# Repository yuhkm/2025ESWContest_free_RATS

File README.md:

# 2025ESWContest_free_RATS
<br/>

## Driving Assistance Device for Beginner Drivers

<br/>

## System Overview

<br/>

## Team Members
<div align="center">

| **안재원 (팀장)** | **김유환** | **박요한** | **박수현** | **정연홍** |
|:---:|:---:|:---:|:---:|:---:|
|  |  |  |  |  |
| [@JwAhn0830](https://github.com/JwAhn0830) | [@yuhkm](https://github.com/yuhkm) | [@doct-vg](https://github.com/doct-vg) | [@jstrfunctionk](https://github.com/strfunctionk) | [@zyh3569](https://github.com/zyh3569) |
| [Main Device (Gaze),](https://github.com/yuhkm/2025ESWContest_free_RATS/tree/main/Main_Device/gaze)<br/>[Server Communication](https://github.com/yuhkm/2025ESWContest_free_RATS/tree/main/Main_Device) | [Main Device (Lane),](https://github.com/yuhkm/2025ESWContest_free_RATS/tree/main/Main_Device/LDS)<br/>[HUD](https://github.com/yuhkm/2025ESWContest_free_RATS/tree/main/HUD) | [Vehicle Sensors,](https://github.com/yuhkm/2025ESWContest_free_RATS/tree/main/Main_Device/VDP)<br/>[CAD](https://github.com/yuhkm/2025ESWContest_free_RATS/tree/main/HW) | [Backend](https://github.com/yuhkm/2025ESWContest_free_RATS/tree/main/Backend) | [Frontend](https://github.com/yuhkm/2025ESWContest_free_RATS/tree/main/Frontend) |

</div>
<br/>

## Demo
- [YouTube](https://www.youtube.com/watch?v=WTc7l_RPrZw)  
<br/>

## Repo
- [Main Device](https://github.com/yuhkm/2025ESWContest_free_RATS/tree/main/Main_Device)  
- [HUD](https://github.com/yuhkm/2025ESWContest_free_RATS/tree/main/HUD)
- [Backend](https://github.com/yuhkm/2025ESWContest_free_RATS/tree/main/Backend)  
- [Frontend](https://github.com/yuhkm/2025ESWContest_free_RATS/tree/main/Frontend)  
- [HW](https://github.com/yuhkm/2025ESWContest_free_RATS/tree/main/HW)
<br/>

<br/>

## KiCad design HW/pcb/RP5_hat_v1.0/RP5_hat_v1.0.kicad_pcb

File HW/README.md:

# HW
- CAD
  - SolidWorks
- PCB
  - KiCAD  

<br>

## CAD

### Raspberry Pi 5 case  

### HUD case  

### Camera case  

### IMU case  

<br>
<br>

## PCB

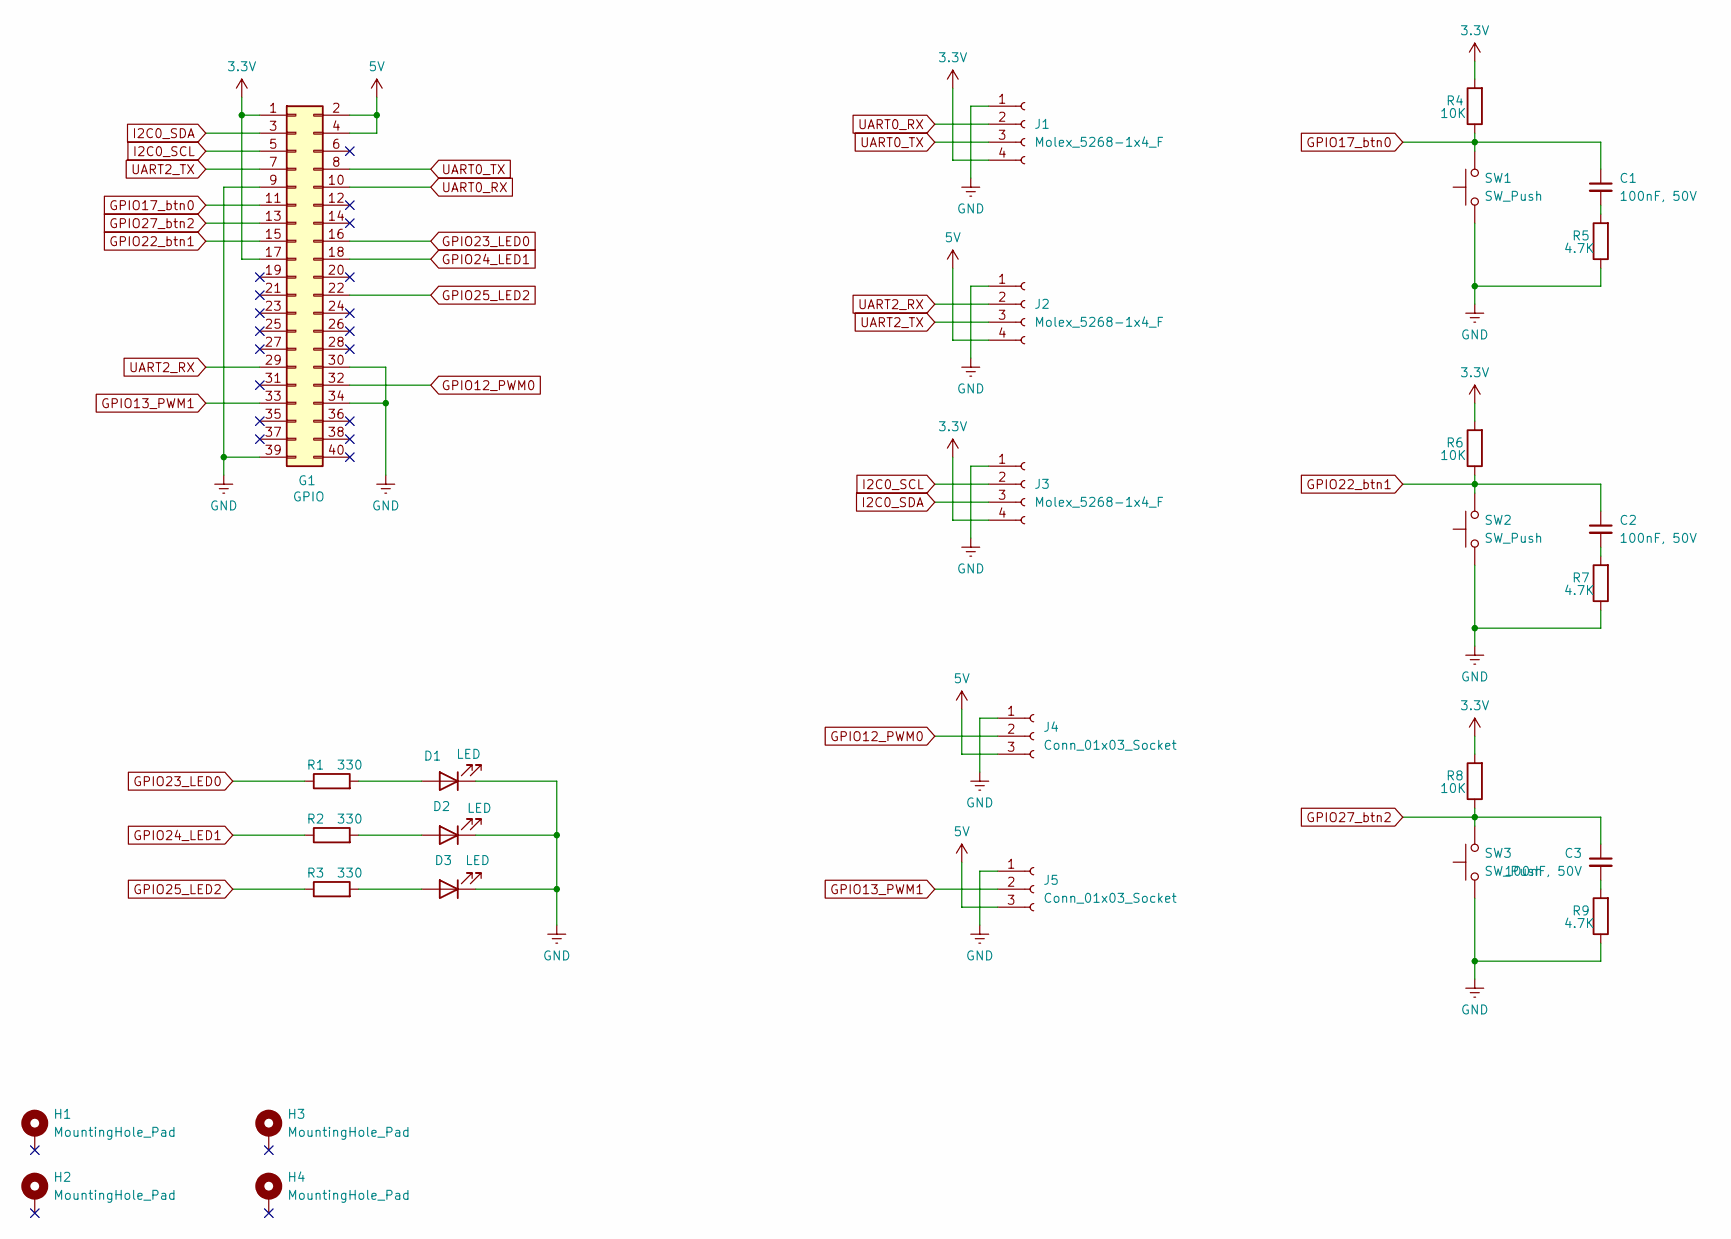
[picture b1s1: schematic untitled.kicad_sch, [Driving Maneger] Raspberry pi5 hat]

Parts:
C1, C2, C3: 100nF, 50V; CP_Radial_D5.0mm_P2.50mm
D1, D2, D3: LED; LED_D3.0mm
G1: GPIO; PinHeader_2x20_P2.54mm_Vertical
H1, H2, H3, H4: MountingHole_Pad; MountingHole_2.7mm_M2.5_DIN965_Pad_TopBottom
J1, J2, J3: Molex_5268-1x4_F; Molex_SPOX_5267-04A_1x04_P2.50mm_Vertical
J4, J5: Conn_01x03_Socket; Molex_SPOX_5267-03A_1x03_P2.50mm_Vertical
R1, R2, R3: 330; R_Axial_DIN0204_L3.6mm_D1.6mm_P7.62mm_Horizontal
R4, R6, R8: 10K; R_Axial_DIN0204_L3.6mm_D1.6mm_P7.62mm_Horizontal
R5, R7, R9: 4.7K; R_Axial_DIN0204_L3.6mm_D1.6mm_P7.62mm_Horizontal
SW1, SW2, SW3: SW_Push; SW_PUSH_6mm

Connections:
3.3V: G1.1, G1.17, J1.4, J3.4, R4.2, R6.2, R8.2
5V: G1.2, G1.4, J2.4, J4.3, J5.3
GND: D1.1 (K), D2.1 (K), D3.1 (K), G1.9, G1.30, G1.34, G1.39, J1.1, J2.1, J3.1, J4.1, J5.1, R5.1, R7.1, R9.1, SW1.1, SW2.1, SW3.1
GPIO12_PWM0: G1.32, J4.2
GPIO13_PWM1: G1.33, J5.2
GPIO17_btn0: C1.1, G1.11, R4.1, SW1.2
GPIO22_btn1: C2.1, G1.15, R6.1, SW2.2
GPIO23_LED0: G1.16, R1.1
GPIO24_LED1: G1.18, R2.1
GPIO25_LED2: G1.22, R3.1
GPIO27_btn2: C3.1, G1.13, R8.1, SW3.2
I2C0_SCL: G1.5, J3.2
I2C0_SDA: G1.3, J3.3
unnamed: C1.2, R5.2
unnamed: C2.2, R7.2
unnamed: C3.2, R9.2
unnamed: D1.2 (A), R1.2
unnamed: D2.2 (A), R2.2
unnamed: D3.2 (A), R3.2
UART0_RX: G1.10, J1.2
UART0_TX: G1.8, J1.3
UART2_RX: G1.29, J2.2
UART2_TX: G1.7, J2.3

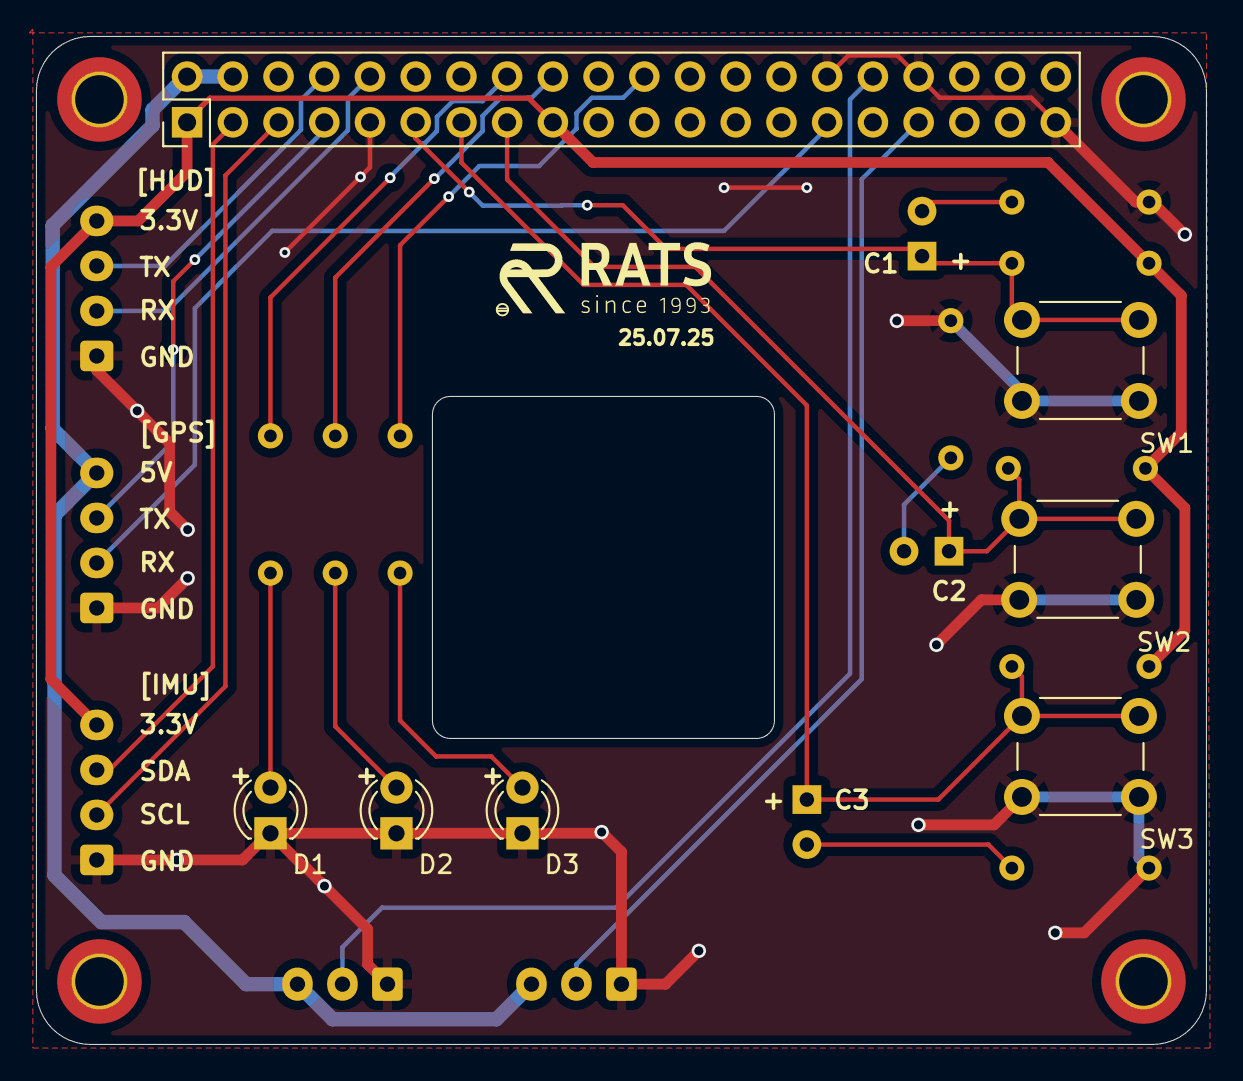
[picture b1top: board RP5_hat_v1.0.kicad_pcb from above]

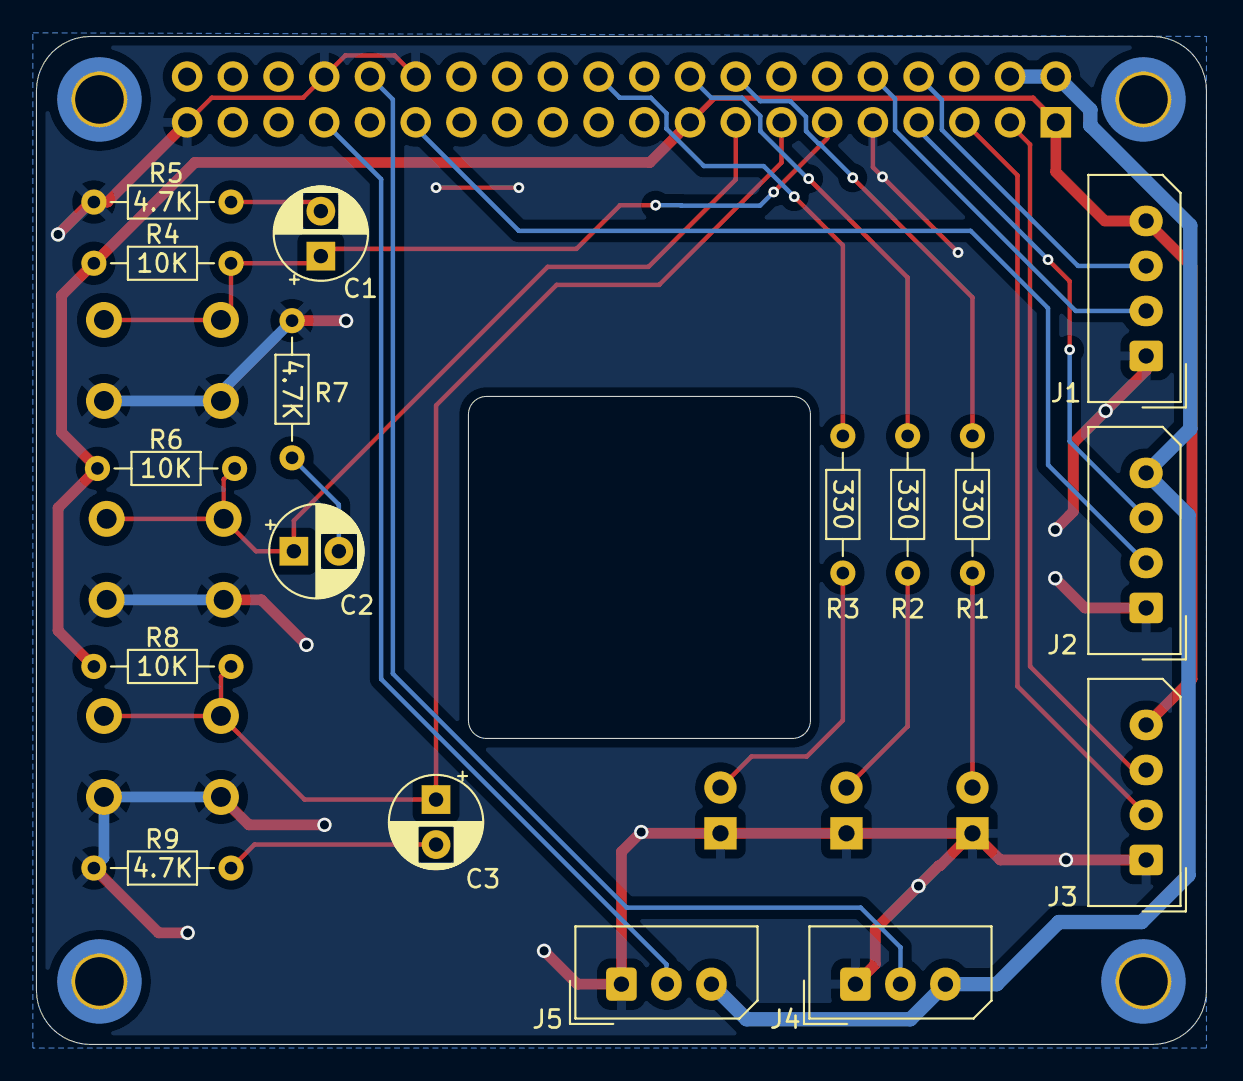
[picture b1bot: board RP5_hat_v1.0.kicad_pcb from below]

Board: 2 copper layers, 65.0 x 56.0 mm, 28 parts (17 on the bottom side), 23 nets.

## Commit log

2025-09-03 Update : ESW project commit
2025-09-03 Update : Update README
